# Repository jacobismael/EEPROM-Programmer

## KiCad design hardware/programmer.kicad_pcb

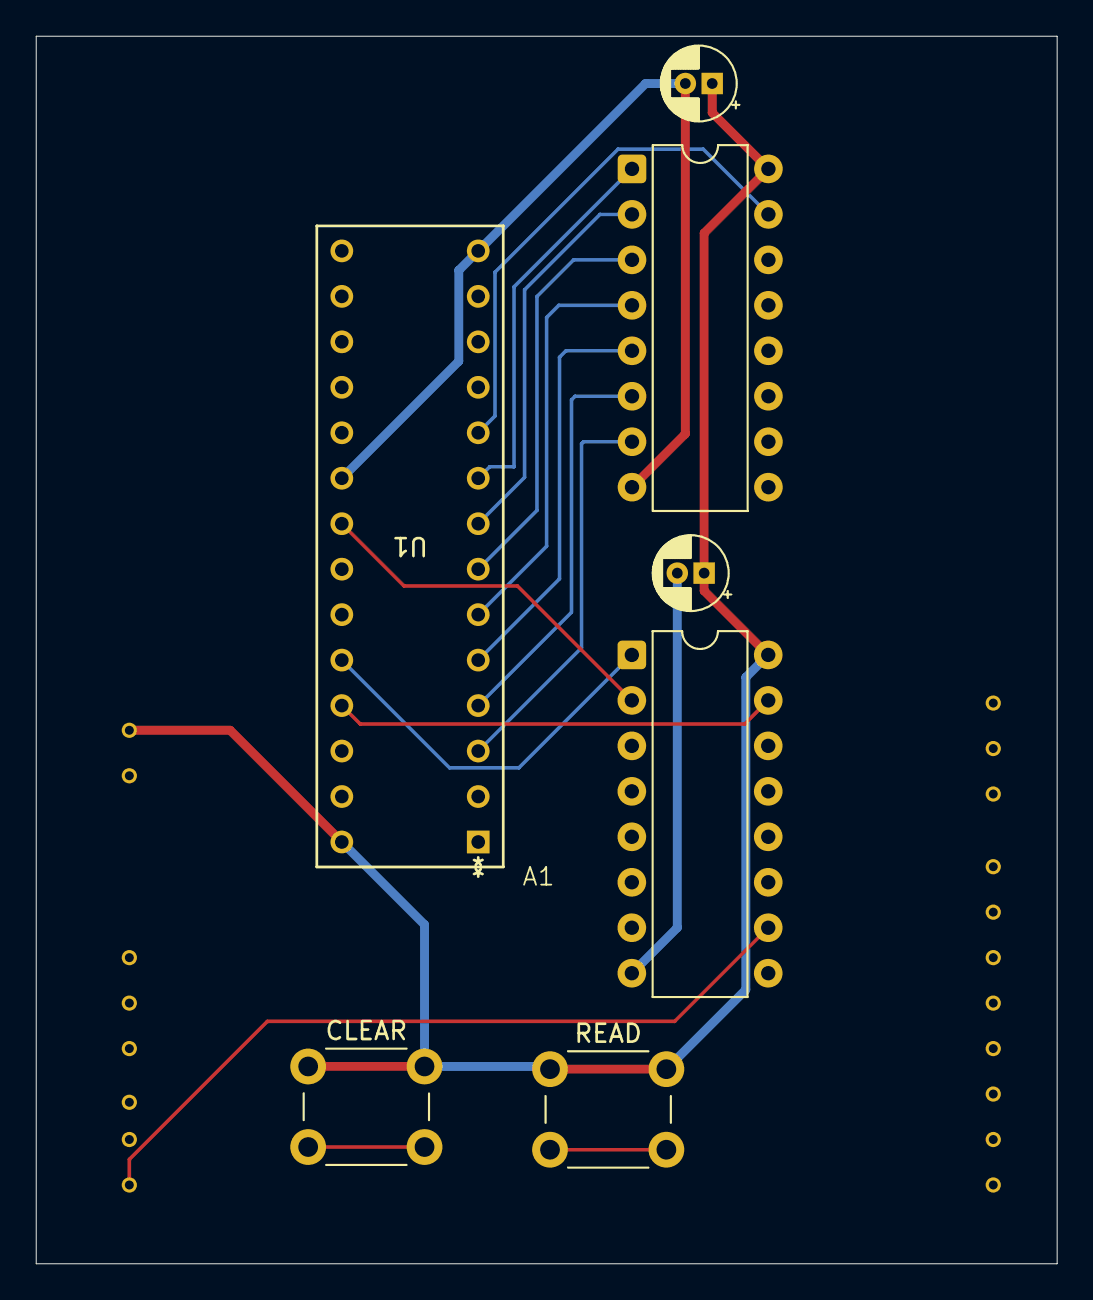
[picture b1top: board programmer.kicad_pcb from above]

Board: 2 copper layers, 57.0 x 68.6 mm, 8 parts (0 on the bottom side), 31 nets.

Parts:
A1: Arduino_UNO_R3; eeprom_programmer
C1, C2: 0.1uF; CP_Radial_D4.0mm_P1.50mm
CLEAR: SW_Push_Dual; SW_PUSH_6mm
READ: SW_Push_Dual; SW_PUSH_6mm
U1: CONN_110-99-328-41-001000_MIM
U2, U3: 74HC595; CERDIP-16_W7.62mm_SideBrazed

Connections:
+5V: A1.5 (+5V), C1.1, C2.1, CLEAR.1, READ.1, U1.28 (VCC), U2.16 (VCC), U3.16 (VCC)
ADDR: A1.9 (A0), U2.14 (SER)
A_{0}: U1.10 (A0), U2.15 (QA)
A_{1}: U1.9 (A1), U2.1 (QB)
A_{2}: U1.8 (A2), U2.2 (QC)
A_{3}: U1.7 (A3), U2.3 (QD)
A_{4}: U1.6 (A4), U2.4 (QE)
A_{5}: U1.5 (A5), U2.5 (QF)
A_{6}: U1.4 (A6), U2.6 (QG)
A_{7}: U1.3 (A7), U2.7 (QH)
A_{8}: U1.25 (A8), U3.15 (QA)
A_{9}: U1.24 (A9), U3.1 (QB)
A_{10}: U1.21 (A10), U3.2 (QC)
CLK: A1.10 (A1), U2.11 (SRCLK), U2.12 (RCLK), U3.11 (SRCLK), U3.12 (RCLK)
CLR: A1.24 (D9), CLEAR.2
GND: A1.6 (GND), C1.2, C2.2, U1.14 (GND), U1.20 (~CE), U2.8 (GND), U3.8 (GND)
I/O0: A1.15 (D0/RX), U1.11 (I/O0)
I/O1: A1.16 (D1/TX), U1.12 (I/O1)
I/O2: A1.17 (D2), U1.13 (I/O2)
I/O3: A1.18 (D3), U1.15 (I/O3)
I/O4: A1.19 (D4), U1.16 (I/O4)
I/O5: A1.20 (D5), U1.17 (I/O5)
I/O6: A1.21 (D6), U1.18 (I/O6)
I/O7: A1.22 (D7), U1.19 (I/O7)
unnamed: U2.9 (QH'), U3.14 (SER)
RDY/~BUSY: A1.25 (D10), U1.1 (RDY/~BUSY)
READ: A1.23 (D8), READ.2
~LATCH: A1.11 (A2), U2.13 (~OE), U3.13 (~OE)
~OE: A1.13 (SDA/A4), U1.22 (~OE)
~RESET: A1.14 (SCL/A5), U2.10 (~SRCLR), U3.10 (~SRCLR)
~WE: A1.12 (A3), U1.27 (~WE)

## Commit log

2025-06-18 initial commit{
2025-06-18 merge
2025-06-18 Create LICENSE
2025-07-09 reorg
2025-07-09 add firmware stub
2025-07-09 test
2025-07-19 modified schematic for system assembly
2025-07-19 updated schematic files
2025-07-29 intial firmware
